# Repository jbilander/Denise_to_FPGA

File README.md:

# Denise_to_FPGA
A small adapter-board that connects 12-bit RGB, 14 MHz CLK, PIXELSW and SYNC-signals on Denise to a FPGA-board via a 5V-tolerant buffer.
A synchronous 14 MHz clock is generated from `C7M XOR CDAC` by using a `74LVC1G86`-chip. This will be fed into the FPGA's PLL.

Board is two layers.

WORK IN PROGRESS, NOT FULLY TESTED YET!

***

***

<br />

***
BOM Rev. A
---------
Designator  | Name/Value   | Package | Notes
-|-|-|-|
U1 | Voltage Regulator 3.3V, <br /> LM1117-3.3 or <br /> AMS1117-3.3 | SOT-223 | 3.3V 1A Low Drop-Out (LDO) [Voltage regulator](https://www.aliexpress.com/item/32869037691.html).
U2,U3 | Bus Transceiver 74LVC245A  | TSSOP-20 | [74LVC245APW-T](https://www.mouser.com/ProductDetail/771-74LVC245APW-T)
U4 | XOR Gate 74LVC1G86 | SOT-353 | [74LVC1G86](https://www.mouser.com/ProductDetail/621-74LVC1G86QSE-7)
U5 | 48 pcs TH socket pins | 100 Pcs | IC Leads Receptacle, Length 9.7 mm gold or nickel plated.<br />[100 pcs](https://www.aliexpress.com/item/1005002830101899.html)<br />[300 pcs](https://www.aliexpress.com/item/1005004707554342.html)<br />[1000 pcs](https://www.aliexpress.com/item/32972142300.html)<br />[1000 pcs](https://www.aliexpress.com/item/32791545218.html)
C1,C2 | Capacitor 10uF | 1206 | Caps for Voltage Regulator
C3-C6 | Capacitor 0.1uF = 100nF | 0805 | Decoupling caps
R1 | 22 or 33 Ω Resistor | 0805 | 22 or 33 Ω series resistor to [avoid reflections](https://embeddeddesignblog.blogspot.com/2022/07/why-do-we-need-series-resistor-on-clock.html) on the 14 MHz CLK
J1 | CDAC/CSYNC Two-Pin Header 2.54mm pitch | 2.54mm pitch | Connect a fly-lead here for old Rev. 3 A500 Motherboard that doesn't have these signals at the Denise socket. 
J2 | VSYNC/HSYNC Two-Pin Header 2.54mm pitch | 2.54mm pitch | Connect a fly-lead here with connection to the Horizontal and Vertical sync on DB23-backside. 
J3 | FPC connector, Right Angle, bottom contact | 0.5mm pitch, 40 positions | [TE Connectivity 4-1734592-0](https://www.mouser.com/ProductDetail/571-4-1734592-0) or [40p here](https://www.aliexpress.com/item/10000000478377.html)

***

[![CC BY-SA 4.0][cc-by-sa-shield]][cc-by-sa]

This work is licensed under a
[Creative Commons Attribution-ShareAlike 4.0 International License][cc-by-sa].

[![CC BY-SA 4.0][cc-by-sa-image]][cc-by-sa]

[cc-by-sa]: http://creativecommons.org/licenses/by-sa/4.0/
[cc-by-sa-image]: https://licensebuttons.net/l/by-sa/4.0/88x31.png
[cc-by-sa-shield]: https://img.shields.io/badge/License-CC%20BY--SA%204.0-lightgrey.svg

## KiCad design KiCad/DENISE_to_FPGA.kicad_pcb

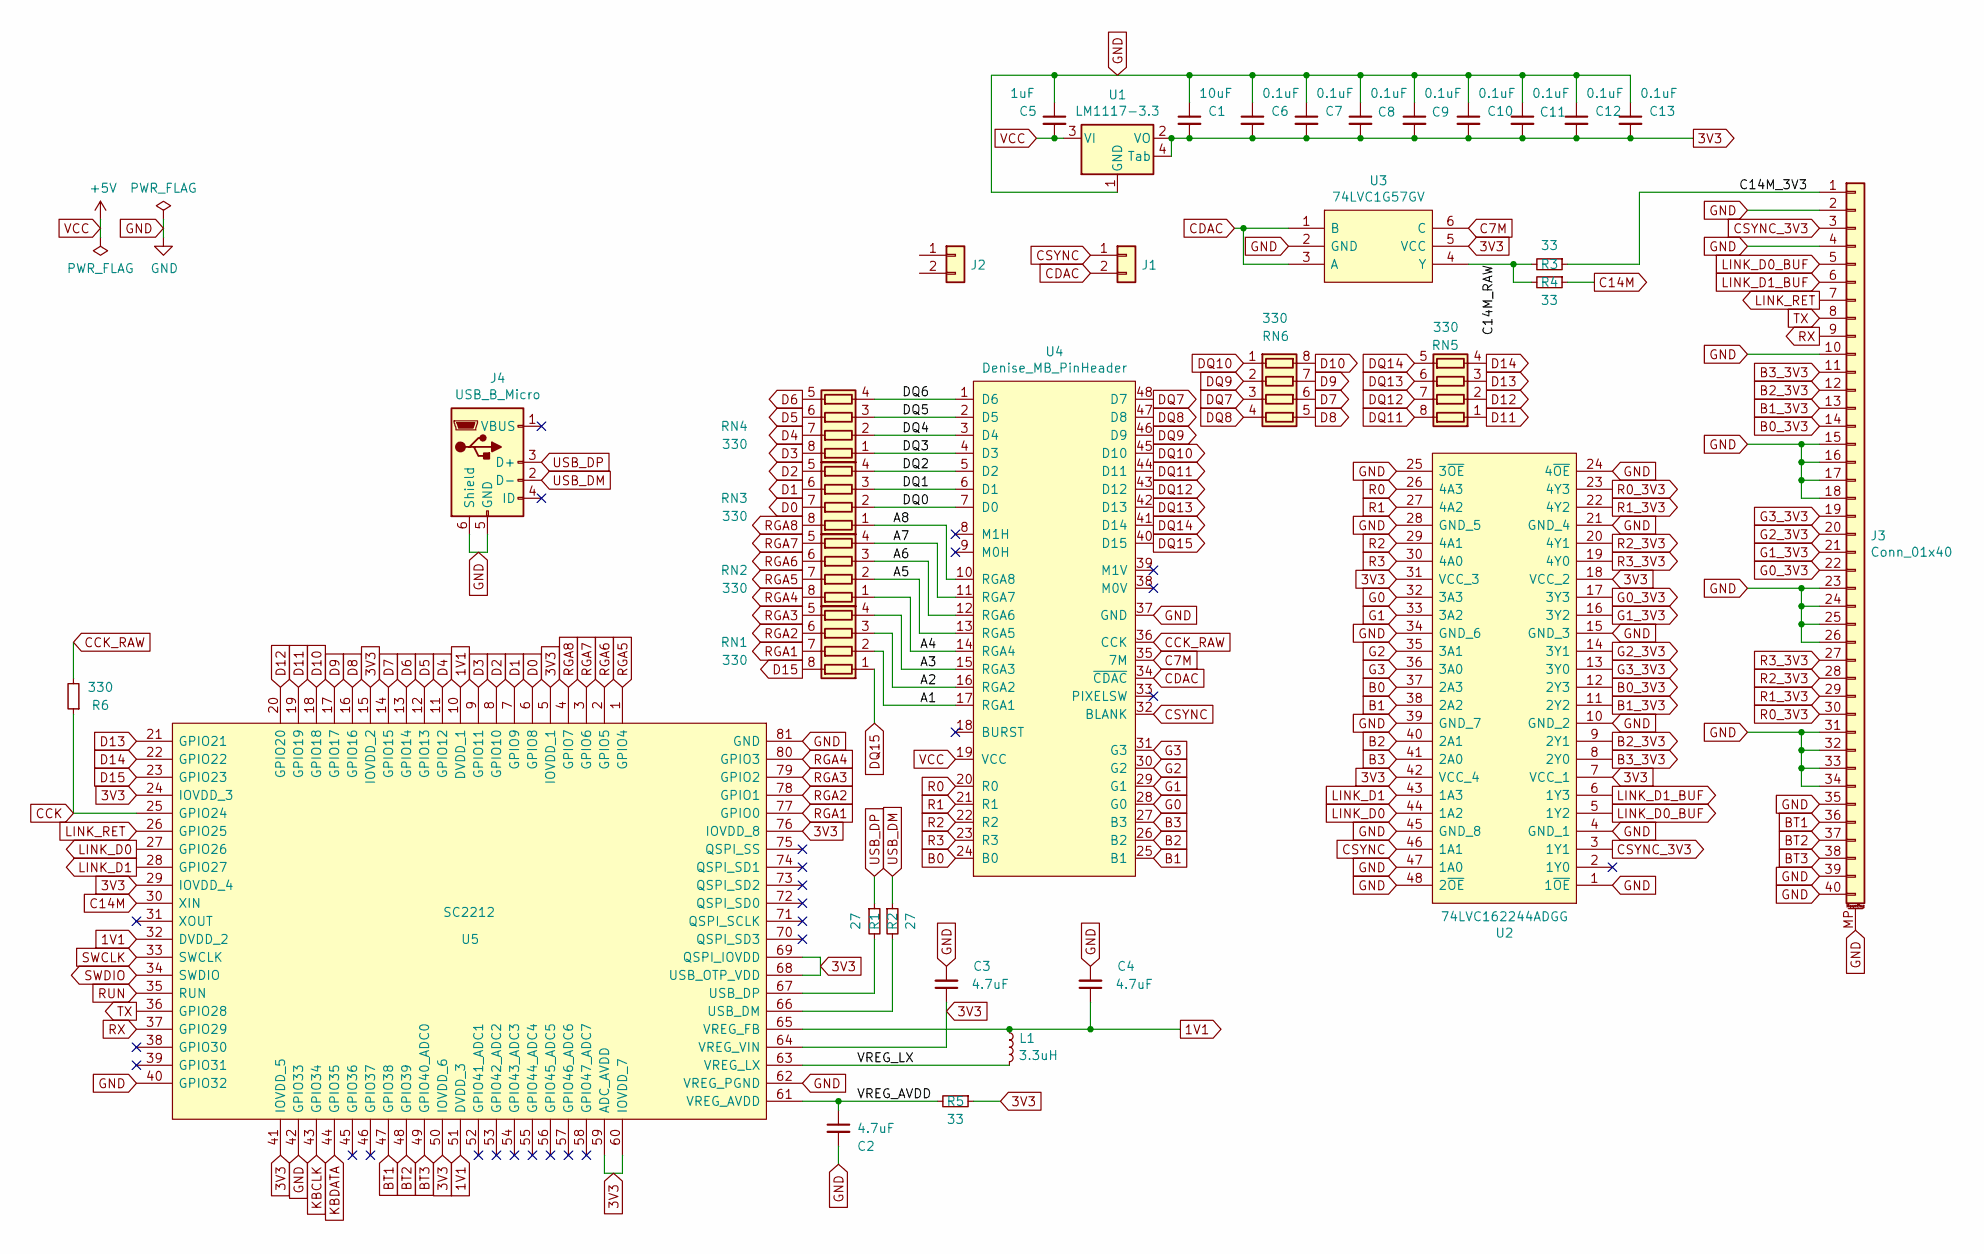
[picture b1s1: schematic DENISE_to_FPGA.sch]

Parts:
C1: 10uF; C_1206_3216Metric_Pad1.42x1.75mm_HandSolder
C2, C3, C4: 4.7uF; C_1206_3216Metric_Pad1.33x1.80mm_HandSolder
C5: 1uF; C_0805_2012Metric_Pad1.18x1.45mm_HandSolder
C6, C7, C8, C9: 0.1uF; C_0805_2012Metric_Pad1.15x1.4mm_HandSolder
C10, C11, C12, C13: 0.1uF; C_0603_1608Metric_Pad1.08x0.95mm_HandSolder
J1, J2: Conn_01x02; PinHeader_1x02_P2.54mm_Horizontal
J3: Conn_01x40; Hirose_FH12-40S-0.5SH_1x40-1MP_P0.50mm_Horizontal
J4: USB_B_Micro; 101181940001LF
L1: 3.3uH; AOTAB201610S3R3101T
R1, R2: 27; R_0603_1608Metric_Pad0.98x0.95mm_HandSolder
R3, R4, R5: 33; R_0603_1608Metric_Pad0.98x0.95mm_HandSolder
R6: 330; R_0603_1608Metric_Pad0.98x0.95mm_HandSolder
RN1, RN2, RN3, RN4, RN5, RN6: 330; R_Array_Convex_4x0603
U1: LM1117-3.3; SOT-223
U2: 74LVC162244ADGG; TSSOP-48_6.1x12.5mm_P0.5mm
U3: 74LVC1G57GV; TSOP-6_1.65x3.05mm_P0.95mm
U4: Denise_MB_PinHeader; DIP-48_W15.24mm_Socket_LongPads
U5: SC2212; QFN40P1000X1000X90-81N-D_handsolder

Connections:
1V1: C4.1, L1.1, U5.10 (DVDD_1), U5.32 (DVDD_2), U5.51 (DVDD_3), U5.65 (VREG_FB)
3V3: C1.2, C3.1, C6.2, C7.2, C8.2, C9.2, C10.2, C11.2, C12.2, C13.2, R5.1, U1.2 (VO), U1.4 (Tab), U2.7 (VCC_1), U2.18 (VCC_2), U2.31 (VCC_3), U2.42 (VCC_4), U3.5 (VCC), U5.5 (IOVDD_1), U5.15 (IOVDD_2), U5.24 (IOVDD_3), U5.29 (IOVDD_4), U5.41 (IOVDD_5), U5.50 (IOVDD_6), U5.59 (ADC_AVDD), U5.60 (IOVDD_7), U5.64 (VREG_VIN), U5.68 (USB_OTP_VDD), U5.69 (QSPI_IOVDD), U5.76 (IOVDD_8)
/A1: RN1.2 (R2.1), U4.17 (RGA1)
/A2: RN1.3 (R3.1), U4.16 (RGA2)
/A3: RN1.4 (R4.1), U4.15 (RGA3)
/A4: RN2.1 (R1.1), U4.14 (RGA4)
/A5: RN2.2 (R2.1), U4.13 (RGA5)
/A6: RN2.3 (R3.1), U4.12 (RGA6)
/A7: RN2.4 (R4.1), U4.11 (RGA7)
/A8: RN3.1 (R1.1), U4.10 (RGA8)
/C14M_3V3: J3.1, R3.1
/C14M_RAW: R3.2, R4.2, U3.4 (Y)
/DQ0: RN3.2 (R2.1), U4.7 (D0)
/DQ1: RN3.3 (R3.1), U4.6 (D1)
/DQ2: RN3.4 (R4.1), U4.5 (D2)
/DQ3: RN4.1 (R1.1), U4.4 (D3)
/DQ4: RN4.2 (R2.1), U4.3 (D4)
/DQ5: RN4.3 (R3.1), U4.2 (D5)
/DQ6: RN4.4 (R4.1), U4.1 (D6)
/VREG_AVDD: C2.1, R5.2, U5.61 (VREG_AVDD)
/VREG_LX: L1.2, U5.63 (VREG_LX)
B0: U2.37 (2A3), U4.24 (B0)
B0_3V3: J3.14, U2.12 (2Y3)
B1: U2.38 (2A2), U4.25 (B1)
B1_3V3: J3.13, U2.11 (2Y2)
B2: U2.40 (2A1), U4.26 (B2)
B2_3V3: J3.12, U2.9 (2Y1)
B3: U2.41 (2A0), U4.27 (B3)
B3_3V3: J3.11, U2.8 (2Y0)
BT1: J3.36, U5.47 (GPIO38)
BT2: J3.37, U5.48 (GPIO39)
BT3: J3.38, U5.49 (GPIO40_ADC0)
C7M: U3.6 (C), U4.35 (7M)
C14M: R4.1, U5.30 (XIN)
CCK: R6.1, U5.25 (GPIO24)
CCK_RAW: R6.2, U4.36 (CCK)
CDAC: J1.2, U3.1 (B), U3.3 (A), U4.34 (~CDAC)
CSYNC: J1.1, U2.46 (1A1), U4.32 (BLANK)
CSYNC_3V3: J3.3, U2.3 (1Y1)
D0: RN3.7 (R2.2), U5.6 (GPIO8)
D1: RN3.6 (R3.2), U5.7 (GPIO9)
D2: RN3.5 (R4.2), U5.8 (GPIO10)
D3: RN4.8 (R1.2), U5.9 (GPIO11)
D4: RN4.7 (R2.2), U5.11 (GPIO12)
D5: RN4.6 (R3.2), U5.12 (GPIO13)
D6: RN4.5 (R4.2), U5.13 (GPIO14)
D7: RN6.6 (R3.2), U5.14 (GPIO15)
D8: RN6.5 (R4.2), U5.16 (GPIO16)
D9: RN6.7 (R2.2), U5.17 (GPIO17)
D10: RN6.8 (R1.2), U5.18 (GPIO18)
D11: RN5.1 (R1.1), U5.19 (GPIO19)
D12: RN5.2 (R2.1), U5.20 (GPIO20)
D13: RN5.3 (R3.1), U5.21 (GPIO21)
D14: RN5.4 (R4.1), U5.22 (GPIO22)
D15: RN1.8 (R1.2), U5.23 (GPIO23)
DQ7: RN6.3 (R3.1), U4.48 (D7)
DQ8: RN6.4 (R4.1), U4.47 (D8)
DQ9: RN6.2 (R2.1), U4.46 (D9)
DQ10: RN6.1 (R1.1), U4.45 (D10)
DQ11: RN5.8 (R1.2), U4.44 (D11)
DQ12: RN5.7 (R2.2), U4.43 (D12)
DQ13: RN5.6 (R3.2), U4.42 (D13)
DQ14: RN5.5 (R4.2), U4.41 (D14)
DQ15: RN1.1 (R1.1), U4.40 (D15)
G0: U2.32 (3A3), U4.28 (G0)
G0_3V3: J3.22, U2.17 (3Y3)
G1: U2.33 (3A2), U4.29 (G1)
G1_3V3: J3.21, U2.16 (3Y2)
G2: U2.35 (3A1), U4.30 (G2)
G2_3V3: J3.20, U2.14 (3Y1)
G3: U2.36 (3A0), U4.31 (G3)
G3_3V3: J3.19, U2.13 (3Y0)
GND: C1.1, C2.2, C3.2, C4.2, C5.1, C6.1, C7.1, C8.1, C9.1, C10.1, C11.1, C12.1, C13.1, J3.2, J3.4, J3.10, J3.15, J3.16, J3.17, J3.18, J3.23, J3.24, J3.25, J3.26, J3.31, J3.32, J3.33, J3.34, J3.35, J3.39, J3.40, J3.MP (MountPin), J4.5 (GND), J4.6 (Shield), U1.1 (GND), U2.1 (1~OE), U2.4 (GND_1), U2.10 (GND_2), U2.15 (GND_3), U2.21 (GND_4), U2.24 (4~OE), U2.25 (3~OE), U2.28 (GND_5), U2.34 (GND_6), U2.39 (GND_7), U2.45 (GND_8), U2.47 (1A0), U2.48 (2~OE), U3.2 (GND), U4.37 (GND), U5.40 (GPIO32), U5.42 (GPIO33), U5.62 (VREG_PGND), U5.81 (GND)
KBCLK: U5.43 (GPIO34)
KBDATA: U5.44 (GPIO35)
LINK_D0: U2.44 (1A2), U5.27 (GPIO26)
LINK_D0_BUF: J3.5, U2.5 (1Y2)
LINK_D1: U2.43 (1A3), U5.28 (GPIO27)
LINK_D1_BUF: J3.6, U2.6 (1Y3)
LINK_RET: J3.7, U5.26 (GPIO25)
unnamed: R1.2, U5.67 (USB_DP)
unnamed: R2.2, U5.66 (USB_DM)
R0: U2.26 (4A3), U4.20 (R0)
R0_3V3: J3.30, U2.23 (4Y3)
R1: U2.27 (4A2), U4.21 (R1)
R1_3V3: J3.29, U2.22 (4Y2)
R2: U2.29 (4A1), U4.22 (R2)
R2_3V3: J3.28, U2.20 (4Y1)
R3: U2.30 (4A0), U4.23 (R3)
R3_3V3: J3.27, U2.19 (4Y0)
RGA1: RN1.7 (R2.2), U5.77 (GPIO0)
RGA2: RN1.6 (R3.2), U5.78 (GPIO1)
RGA3: RN1.5 (R4.2), U5.79 (GPIO2)
RGA4: RN2.8 (R1.2), U5.80 (GPIO3)
RGA5: RN2.7 (R2.2), U5.1 (GPIO4)
RGA6: RN2.6 (R3.2), U5.2 (GPIO5)
RGA7: RN2.5 (R4.2), U5.3 (GPIO6)
RGA8: RN3.8 (R1.2), U5.4 (GPIO7)
RUN: U5.35 (RUN)
RX: J3.9, U5.37 (GPIO29)
SWCLK: U5.33 (SWCLK)
SWDIO: U5.34 (SWDIO)
TX: J3.8, U5.36 (GPIO28)
USB_DM: J4.2 (D-), R2.1
USB_DP: J4.3 (D+), R1.1
VCC: C5.2, U1.3 (VI), U4.19 (VCC)

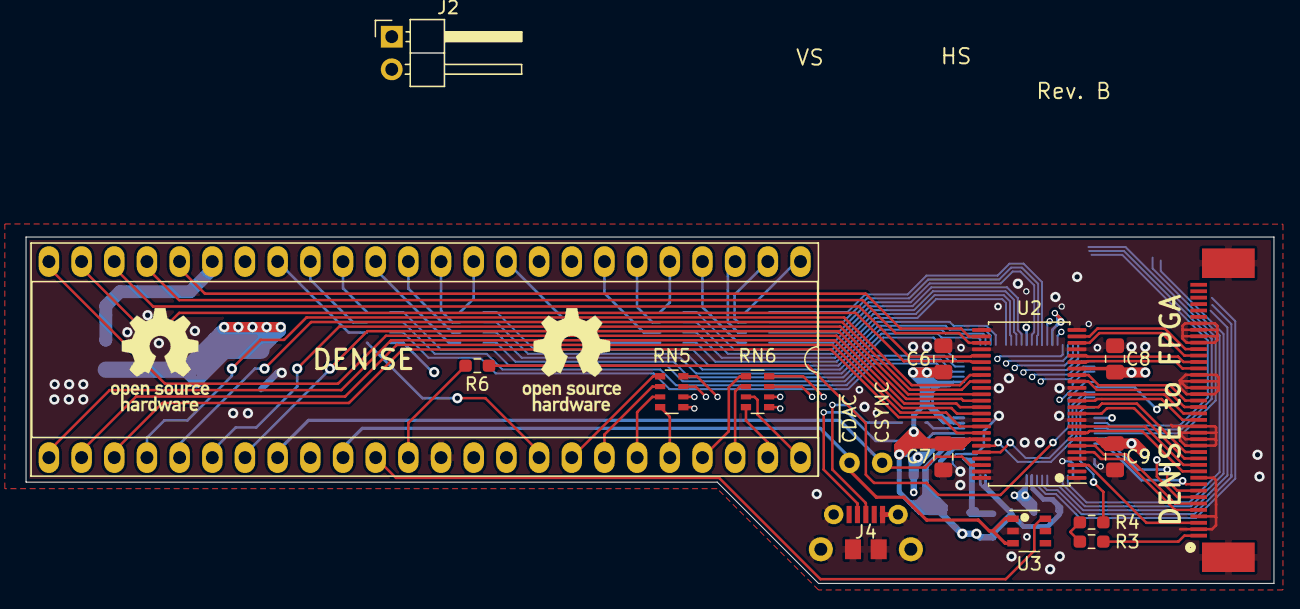
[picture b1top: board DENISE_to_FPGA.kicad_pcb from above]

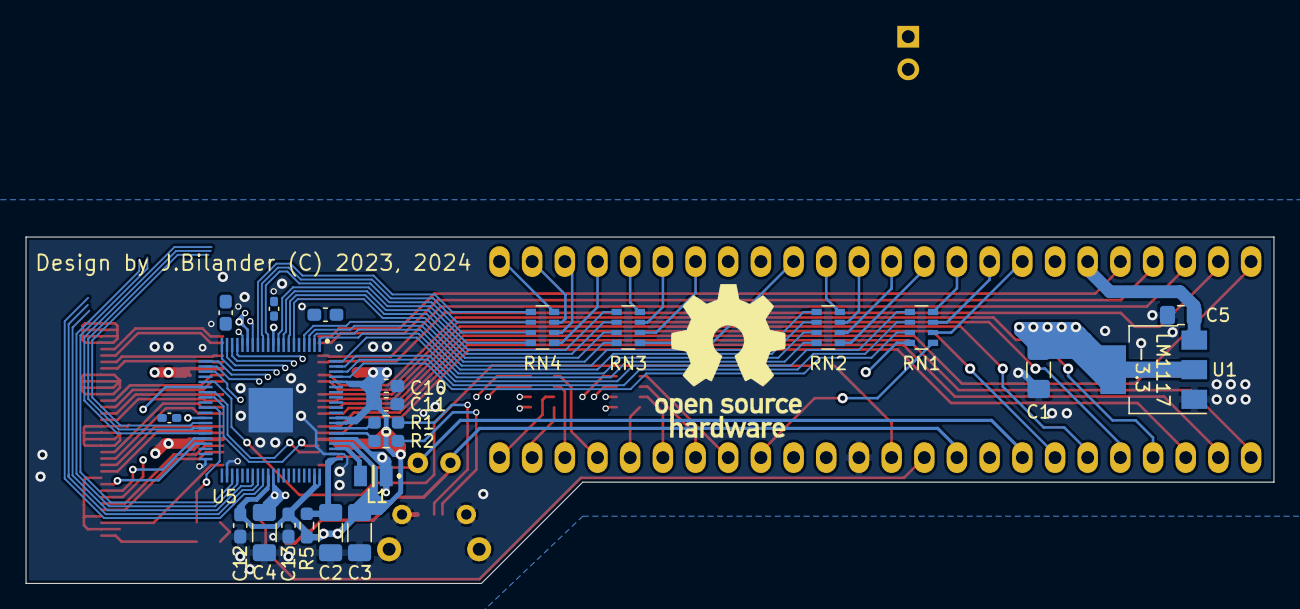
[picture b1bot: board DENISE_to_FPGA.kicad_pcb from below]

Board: 4 copper layers, 97.0 x 26.9 mm, 35 parts (19 on the bottom side), 101 nets.

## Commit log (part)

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2023-08-19 Added KiCAD files
2023-08-20 Added footprint
2023-08-20 New design, more routing done
2023-08-21 Fixed GND-routing on FPC-conn
2023-08-21 Fixed path to footprint directory
2023-08-23 Create LICENSE
2023-09-06 Added 3D-model
2023-09-06 Added a 74LVC1G86 XOR gate and modified the 40-pin FPC to also take a TE Connectivity 4-1734592-0, and added Hsync,Vsync-header
2023-09-07 Added a series resistor for C14M and changed some pin-assignments on the 40-pin FPC
2023-09-07 changed pin assignments on the 40-pin FPC
2023-09-07 Removed unused nets, added no-connect flags
2023-09-07 Added pics
2023-09-11 small adjustment of board length
2023-09-13 small silkscreen fix
2023-09-13 Updated pics
2023-09-13 Added schematic pdf
2023-12-31 Added images
2024-06-19 Updated design with a 74LVC162244ADGG, changed PCB size and TH-pins
2024-06-20 Added 74LVC1G57GV
2024-06-20 changed U3 from 74LVC1G86 (XOR-gate, TSSOP-5) to 74LVC1G57GV (XNOR-gate, TSOP-6)
2024-06-20 silkscreen fix adding dots indicating pin 1 on U2 and U3
2024-06-20 Fixed orientation of U2
2024-06-22 silkscreen fix U2
2024-07-29 Add schematic pdf

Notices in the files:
KiCad/DENISE_to_FPGA.kicad_pcb:
Design by J.Bilander (C) 2023, 2024
